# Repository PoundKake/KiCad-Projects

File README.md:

# KiCad-Projects
Circuit projects and schematics in kicad

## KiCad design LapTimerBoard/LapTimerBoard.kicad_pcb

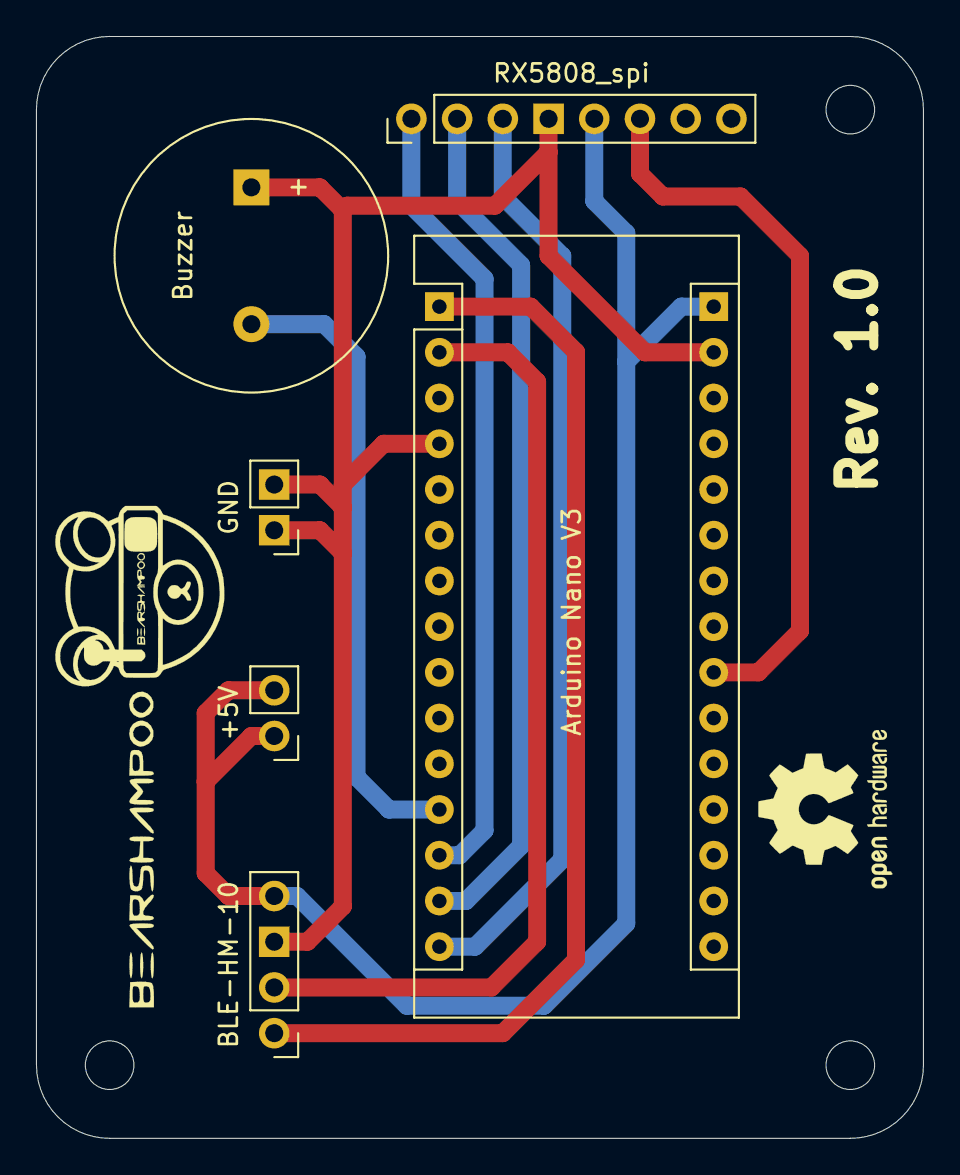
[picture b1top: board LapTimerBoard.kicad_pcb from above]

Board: 2 copper layers, 49.3 x 61.2 mm, 6 parts (0 on the bottom side), 9 nets.

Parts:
+5V: +5V; PinHeader_1x02_P2.54mm_Vertical
Arduino Nano V3: Arduino_Nano_v3.x; Arduino_Nano
BLE-HM-10: BLE-HM-10; PinHeader_1x04_P2.54mm_Vertical
Buzzer: Buzzer; Buzzer_15x7.5RM7.6
GND: GND; PinHeader_1x02_P2.54mm_Vertical
RX5808_spi: RX5808_spi; PinHeader_1x08_P2.54mm_Vertical

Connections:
/CH1: Arduino Nano V3.13, RX5808_spi.1
/CH2: Arduino Nano V3.14, RX5808_spi.2
/CH3: Arduino Nano V3.15, RX5808_spi.3
/RSSI: Arduino Nano V3.22, RX5808_spi.6
GND: Arduino Nano V3.4, Arduino Nano V3.29, BLE-HM-10.3, Buzzer.1, GND.1, GND.2, RX5808_spi.4
unnamed: Arduino Nano V3.1, BLE-HM-10.1
unnamed: Arduino Nano V3.2, BLE-HM-10.2
unnamed: Arduino Nano V3.12, Buzzer.2
VCC: +5V.1, +5V.2, Arduino Nano V3.30, BLE-HM-10.4, RX5808_spi.5

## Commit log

2020-10-06 Initial commit.
2020-10-07 Updated PCB and generated first past of gerber file views.
2020-10-07 Removed temporary gerber files
2020-10-07 updated with edge cuts and mounting holes
2020-10-08 Gerber files generated and bearshampoo assets added into respective folder
2020-10-09 Fixed corrupt grbr files and rezipped them all in .zip file
